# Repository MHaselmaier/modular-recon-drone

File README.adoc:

= Modular Recon Code Repository

Implementation of the drone functionality.

== Required libraries
The project is based on the ESP32 SoC by Espressif. It is possible to use the Arduino IDE to write software for the ESP32 but many developers already experienced a bad support for the chip. The recommanded way is to use Espressif's ESP-IDF. The IDF is a SDK that contains many wrappers for the chips functionality, e.g.: 

* FreeRTOS -> real time operating system for embedded devices
** Tasks
** Semaphores
** Concurrent queues
* TCP/IP stack
** Socket implementation provided by lwip (lightweight ip)
* GPIO abstraction 
* System wide event handler

An instruction on how to install the ESP-IDF is found on their https://esp-idf.readthedocs.io/en/latest/get-started/index.html#setup-toolchain[official developers page].

== Motor Controller

== Main Control Unit
=== Basic Makefile usage
The ESP-IDF provides a pre configured Makefile environment. 

*Build*: make all

*Flash*: make flash -> Implicitly triggers build process

*Clean*: make clean

*Monitor*: make monitor -> ESP toolchain monitor. Use in own terminal as it cannot be killed

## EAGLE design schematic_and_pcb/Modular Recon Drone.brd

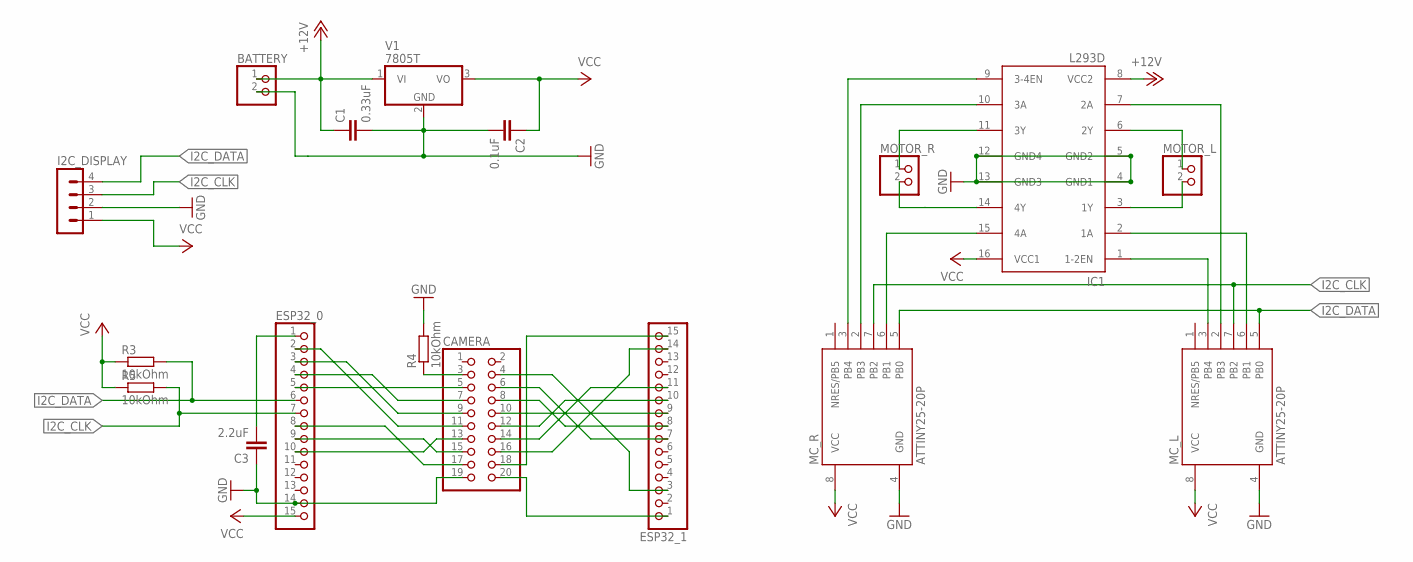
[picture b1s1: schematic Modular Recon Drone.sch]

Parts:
BATTERY: PINHD-1X2; 1X02
C1: 0.33uF; C025-050X050
C2: 0.1uF; C025-050X050
C3: 2.2uF; C025-050X050
CAMERA: PINHD-2X10; 2X10
ESP32_0, ESP32_1: PINHD-1X15; 1X15
I2C_DISPLAY: MA04-1
IC1: L293D; DIL16
MC_L: ATTINY25-20P; PDIP08_300MIL
MC_R: ATTINY25-20P; PDIP08_300MIL
MOTOR_L: PINHD-1X2; 1X02
MOTOR_R: PINHD-1X2; 1X02
R3, R4, R5: 10kOhm; 0204/5
V1: 7805T; TO220H

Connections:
+12V: BATTERY.1, C1.1, IC1.8 (VCC2), V1.1 (VI)
GND: BATTERY.2, C1.2, C2.2, C3.1, CAMERA.19, ESP32_0.14, I2C_DISPLAY.2, IC1.4 (GND1), IC1.5 (GND2), IC1.12 (GND4), IC1.13 (GND3), MC_L.4 (GND), MC_R.4 (GND), R4.2, V1.2 (GND)
I2C_CLK: ESP32_0.7, I2C_DISPLAY.3, MC_L.7 (PB2), MC_R.7 (PB2), R5.2
I2C_DATA: ESP32_0.6, I2C_DISPLAY.4, MC_L.5 (PB0), MC_R.5 (PB0), R3.2
unnamed: IC1.3 (1Y), MOTOR_L.2
unnamed: IC1.6 (2Y), MOTOR_L.1
unnamed: IC1.14 (4Y), MOTOR_R.2
unnamed: IC1.15 (4A), MC_R.6 (PB1)
unnamed: IC1.11 (3Y), MOTOR_R.1
unnamed: IC1.2 (1A), MC_L.6 (PB1)
unnamed: IC1.10 (3A), MC_R.2 (PB3)
unnamed: IC1.7 (2A), MC_L.2 (PB3)
unnamed: IC1.9 (3-4EN), MC_R.3 (PB4)
unnamed: IC1.1 (1-2EN), MC_L.3 (PB4)
unnamed: CAMERA.20, ESP32_1.1
unnamed: CAMERA.18, ESP32_1.15
unnamed: CAMERA.16, ESP32_1.14
unnamed: CAMERA.14, ESP32_1.11
unnamed: CAMERA.12, ESP32_1.10
unnamed: CAMERA.10, ESP32_1.9
unnamed: CAMERA.8, ESP32_1.8
unnamed: CAMERA.6, ESP32_1.7
unnamed: CAMERA.4, ESP32_1.3
unnamed: CAMERA.17, ESP32_0.8
unnamed: CAMERA.15, ESP32_0.9
unnamed: CAMERA.13, ESP32_0.10
unnamed: CAMERA.11, ESP32_0.2
unnamed: CAMERA.9, ESP32_0.3
unnamed: CAMERA.7, ESP32_0.4
unnamed: CAMERA.5, ESP32_0.5
unnamed: CAMERA.3, R4.1
unnamed: C3.2, ESP32_0.1
VCC: C2.1, ESP32_0.15, I2C_DISPLAY.1, IC1.16 (VCC1), MC_L.8 (VCC), MC_R.8 (VCC), R3.1, R5.1, V1.3 (VO)

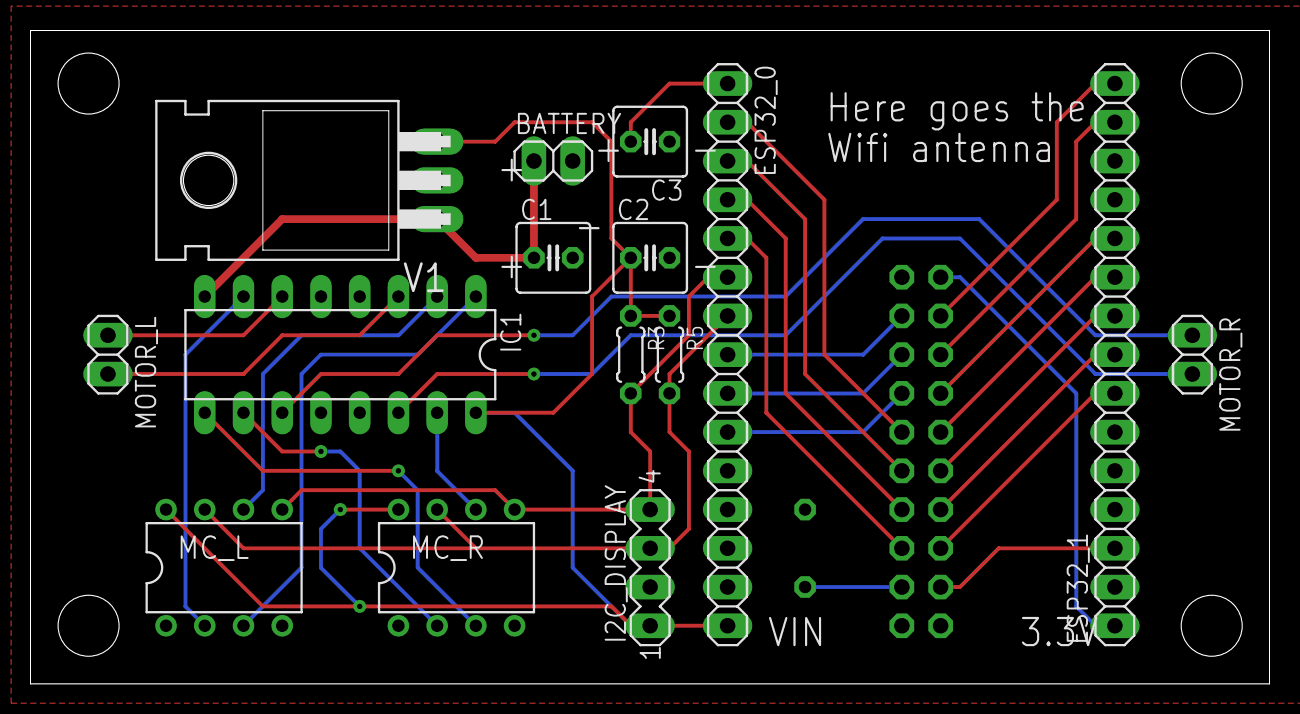
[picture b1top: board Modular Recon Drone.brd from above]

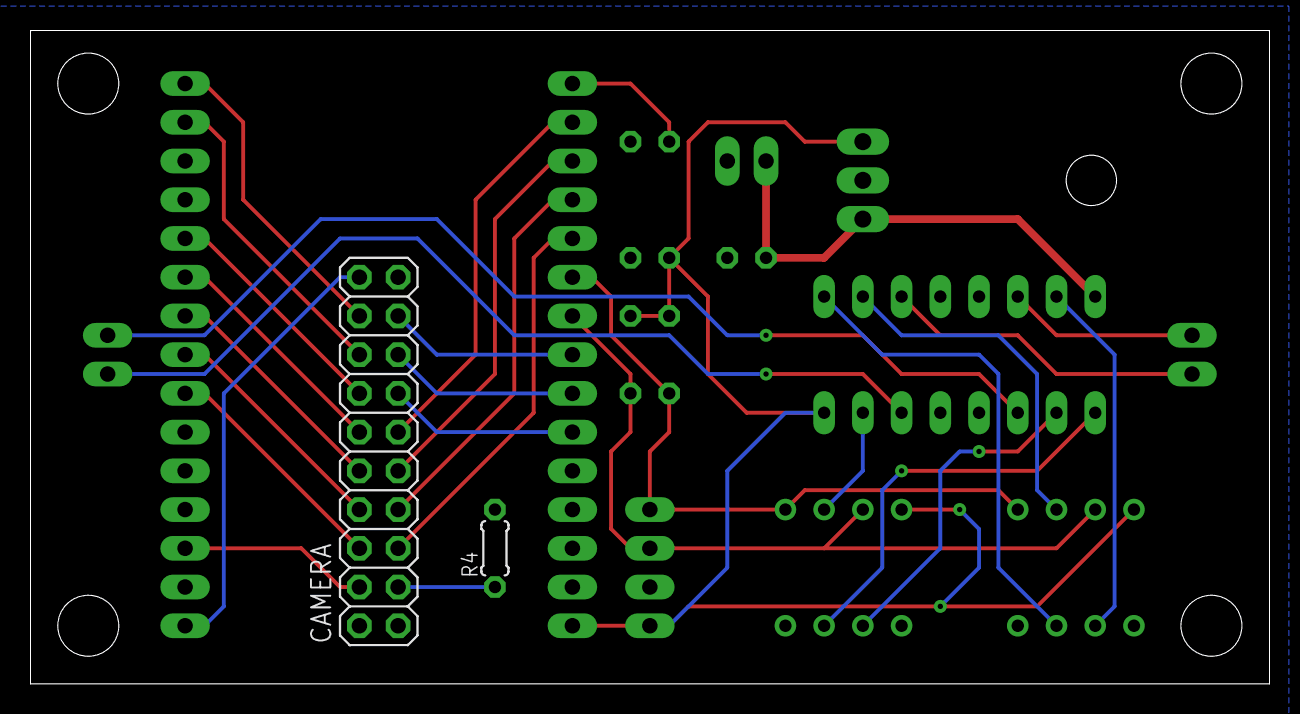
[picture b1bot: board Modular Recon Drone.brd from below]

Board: 2 copper layers, 81.3 x 42.9 mm, 17 parts (2 on the bottom side), 33 nets.

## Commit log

2018-10-18 Initialize motor controll
2018-10-29 Now using C instead of C++. Using usiTwiSlave implementation from: https://github.com/rambo/TinyWire/tree/master Implements ATtiny25 Motorcontroll using I²C.
2018-10-30 Motor is now controlled using two seperate PWMs. Only two H-Bridges are used by one ATtiny. Pin3 can now be used to select either I²C Address 0x01 or 0x02.
2018-11-05 Motor does not spin on startup anymore! Change the starting duty cycle of Timer0 so both PWMs are off on startup
2019-01-07 Restructured project. Added ESP code base to repository. Redone makefile of motor_controller. Renamed files of motor_controller. Rebased README file to root. Added gitignore
2019-01-08 Added makefile support to create both attiny address versions.
2019-01-08 Now only uses one PWM.
2019-01-08 Removed warnings from usi_twi_slave.c.
2019-01-15 Included camera handling library for ov7725 and ov2640 camera modules. Implemented grayscale image streaming functionality. Altered camera library to send additional information to the camera module 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
2019-01-15 Removed esp based motor control which was added for debugging purposes as long as the i2c based motor control didnt work
2019-01-15 Added basic documentation struture to project
2019-01-15 Instead of using the percentage as the duty cycle it is now scaled up to 127 to use the full resolution.
2019-01-15 Made some code refactoring. Also changed the call sequence so the camera socket gets initialized when the AP is up
2019-01-15 Updated documentation. Added links to the screen and camera relevant code repositories
2019-01-16 Included i2c functions again
2019-01-16 Removed unused code (header of image). Altered port delay of i2c, udp server and camera tcp
2019-01-16 Code refactoring (Logging). Removed unused file led.c
2019-01-16 Altered task priority. Lowered resolution
2019-02-18 Added glossary, vision section. Added imgs directory. Wrote parts of camera and display modules hardware section
2019-02-18 Added u8g2 library
2019-02-18 Added description for the motor controller.
2019-02-18 Added eagle project with schematic and pcb layout.
2019-02-18 Added pcb images.
2019-02-18 Added description for power supply.
2019-02-18 Added description for pcb.
2019-02-18 Restructured documentation. Merged hardware and software architecture parts to one architecture part. Refactored figure references to use a counter
2019-02-19 Added reference to usi twi implementation.
2019-02-19 Added Android App.
2019-02-20 - Changed wrapper esp32 library of u8g2 display library -> Removed init code of i2c bus and changed used i2c controller to I2C_NUM_0. - Refactored code - Added display output - Added random number ge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
2019-02-20 Fixed steering and camera rotation.
2019-02-20 Added user interface to connect to recon drone network.
2019-02-20 Added text to MCU description. Updated glossary. Refactored display code. Now displaying signal strength and hskl logo at the beginning
2019-02-20 Removed unused code from drone.h
2019-02-20 Updated doc Makfile.
2019-02-20 Updated MCU text part
2019-02-20 Started deskription of android app.
2019-02-20 Finished App description.
2019-02-20 Renamed server.c into udp_motor_data_server.c. Updated documentation
2019-02-20 Updated MCU text. Fixed section reference error
2019-02-20 Removed random named images
2019-02-20 Refactored Android App implementation.
2019-02-20 Added camera pin connection table.
2019-02-20 Fixed spelling mistakes.
2019-02-20 Renamed Architektur to Aufbau der Drohne.
2019-02-21 Updated texts for MCU, Display
2019-02-21 Added app apk.
2019-02-21 Changed min SDK to 21.
2019-02-21 Added app installation part.
2019-02-21 Added alternative power supply in vision.adoc.
2019-02-21 Minor fixes.
2019-02-22 Added Kameramodul.
2019-02-22 Fixed list.
2019-02-22 Explained why the connection to camera should be short.
2019-02-22 Added breadboard prototype picture
2019-02-22 Updated documentation section MCU.
2019-02-22 Added Lochraster und PCB png.
2019-02-22 Added External Ram Vision and changed to 320x240.
2019-02-22 Added new apk.
2019-02-22 Changed back to 160x120 pixel.
2019-02-22 Added picture of finished drone:
2019-02-22 Added Appendix.
2019-02-22 Extended documentation part MCU
2019-02-22 Added introduction.
2019-02-22 replaced 1 with true
2019-02-22 Updated MCU section of docu
2019-02-22 Added esp kevin
2019-02-22 Added new directory containing documentation sources and general datasheets of the used electrical components
2019-02-22 Added parts to vision
2019-02-22 Added parts to vision of documentation
2019-02-22 Updated documentation part MCU
2019-02-22 Added image of QT control window
2019-02-22 Thomas' changes.
2019-02-22 Added section of qt drone control application to documentation
2019-02-22 Fixes.
2019-02-22 Added last text part to documentation. Added desktop app sources
